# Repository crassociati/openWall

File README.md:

openWall
========

vertical plotting system

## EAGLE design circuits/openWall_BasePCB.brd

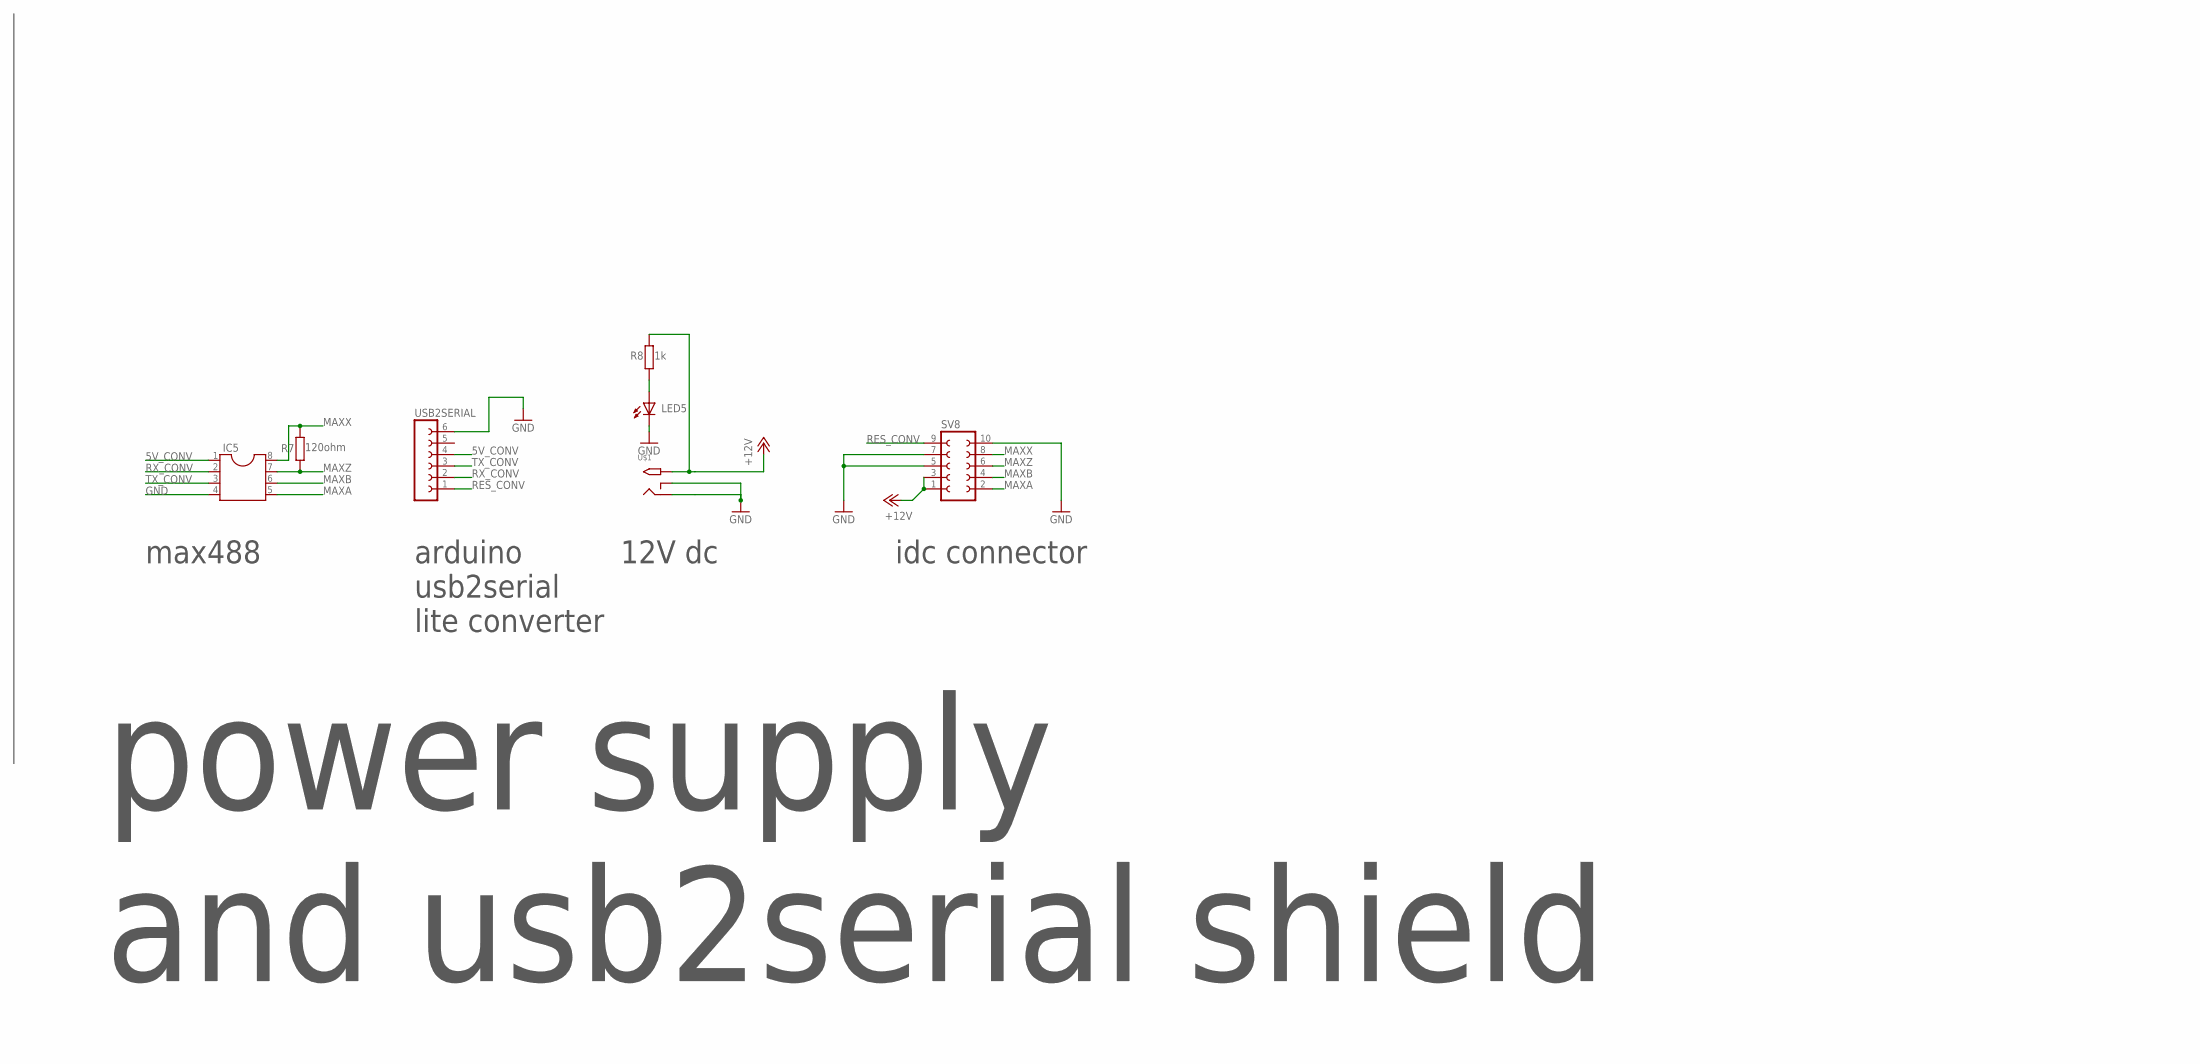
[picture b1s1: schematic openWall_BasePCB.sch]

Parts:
IC5: DIL8; DIL08
LED5: TLLG4400; LED3MM
R7: 120ohm; 0207/7
R8: 1k; 0207/7
SV8: FE05-2
U$1: 2.1MMJACKTHM; PJ-102A
USB2SERIAL: FE06-1; FE06

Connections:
5V_CONV: IC5.1, USB2SERIAL.4
12V: R8.2, U$1.TIP
+12V: SV8.1, SV8.3
GND: IC5.4, LED5.K (C), SV8.5, SV8.7, SV8.10, U$1.RING, U$1.RING_SW, USB2SERIAL.6
MAXA: IC5.5, SV8.2
MAXB: IC5.6, SV8.4
MAXX: IC5.8, R7.2, SV8.8
MAXZ: IC5.7, R7.1, SV8.6
unnamed: LED5.A, R8.1
RES_CONV: SV8.9, USB2SERIAL.1
RX_CONV: IC5.2, USB2SERIAL.2
TX_CONV: IC5.3, USB2SERIAL.3

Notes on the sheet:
arduino usb2serial lite converter
max488
12V dc
idc connector
power supply and usb2serial shield

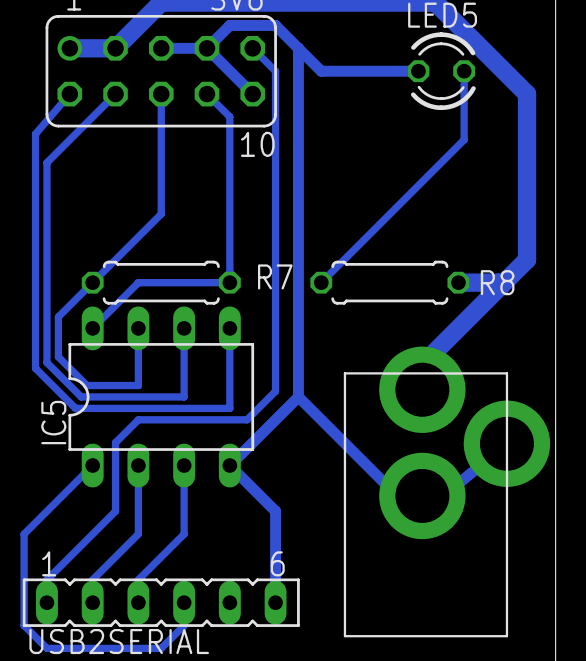
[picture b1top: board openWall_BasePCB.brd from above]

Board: 2 copper layers, 7 parts (0 on the bottom side), 12 nets.

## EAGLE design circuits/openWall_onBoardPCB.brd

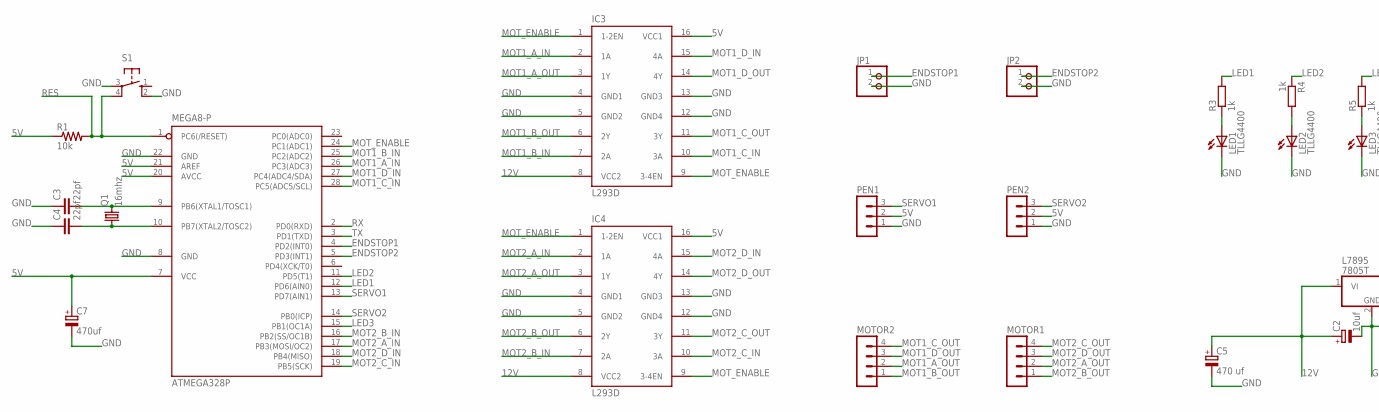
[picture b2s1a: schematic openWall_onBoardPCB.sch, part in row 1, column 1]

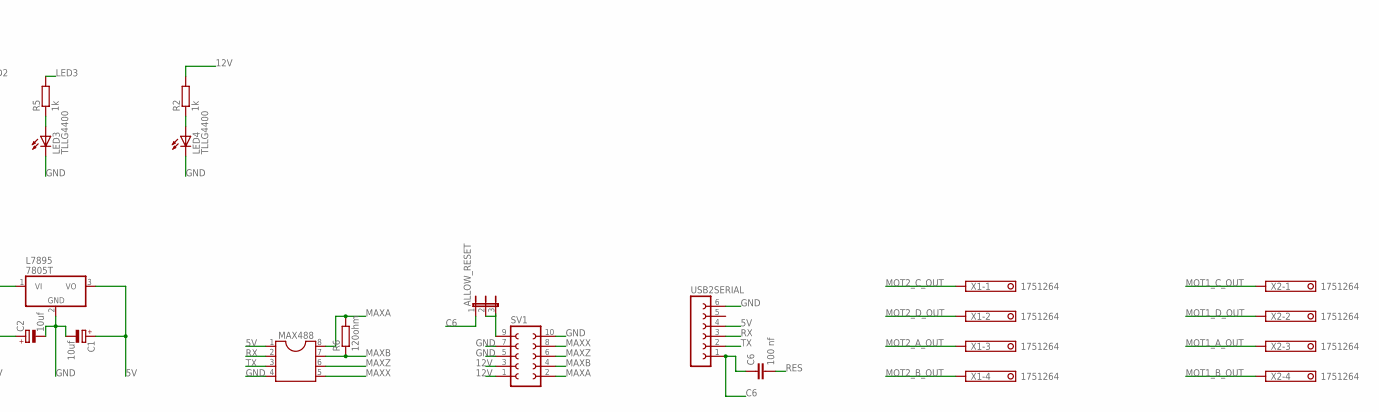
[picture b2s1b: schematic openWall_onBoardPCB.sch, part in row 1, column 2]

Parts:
ALLOW_RESET: JP2E; JP2
ATMEGA328P: MEGA8-P; DIL28-3
C1, C2: 10uf; E2,5-6
C3, C4: 22pf; C025-030X050
C5: 470 uf; E5-6
C6: 100 nf; C050-024X044
C7: 470uf; E5-6
IC3, IC4: L293D; DIL16
JP1, JP2: PINHD-1X2; 1X02
L7895: 7805T; TO220H
LED1, LED2, LED3, LED4: TLLG4400; LED3MM
MAX488: DIL8; DIL08
MOTOR1, MOTOR2: MA04-1
PEN1, PEN2: MA03-1
Q1: 16mhz; HC49/S
R1: 10k; 0207/7
R2: 1k; 0207/7
R3, R4, R5: 1k; 0309V
R6: 120ohm; 0207/7
S1: 10-XX; B3F-10XX
SV1: FE05-2
USB2SERIAL: FE06-1; FE06
X1, X2: 1751264

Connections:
5V: ATMEGA328P.7 (VCC), ATMEGA328P.20 (AVCC), ATMEGA328P.21 (AREF), C1.+, C7.+, IC3.16 (VCC1), IC4.16 (VCC1), L7895.3 (VO), MAX488.1, PEN1.2, PEN2.2, R1.1, USB2SERIAL.4
12V: C2.+, C5.+, IC3.8 (VCC2), IC4.8 (VCC2), L7895.1 (VI), R2.2, SV1.1, SV1.3
C6: ALLOW_RESET.1, C6.1, USB2SERIAL.1
ENDSTOP1: ATMEGA328P.4 (PD2(INT0)), JP1.1
ENDSTOP2: ATMEGA328P.5 (PD3(INT1)), JP2.1
GND: ATMEGA328P.8 (GND), ATMEGA328P.22 (GND), C1.-, C2.-, C3.1, C4.1, C5.-, C7.-, IC3.4 (GND1), IC3.5 (GND2), IC3.12 (GND4), IC3.13 (GND3), IC4.4 (GND1), IC4.5 (GND2), IC4.12 (GND4), IC4.13 (GND3), JP1.2, JP2.2, L7895.2 (GND), LED1.K (C), LED2.K (C), LED3.K (C), LED4.K (C), MAX488.4, PEN1.1, PEN2.1, S1.2 (S1), S1.3, SV1.5, SV1.7, SV1.10, USB2SERIAL.6
LED1: ATMEGA328P.12 (PD6(AIN0)), R3.2
LED2: ATMEGA328P.11 (PD5(T1)), R4.1
LED3: ATMEGA328P.15 (PB1(OC1A)), R5.2
MAXA: MAX488.8, R6.2, SV1.2
MAXB: MAX488.7, R6.1, SV1.4
MAXX: MAX488.5, SV1.8
MAXZ: MAX488.6, SV1.6
MOT1_A_IN: ATMEGA328P.26 (PC3(ADC3)), IC3.2 (1A)
MOT1_A_OUT: IC3.3 (1Y), MOTOR2.2, X2.3
MOT1_B_IN: ATMEGA328P.25 (PC2(ADC2)), IC3.7 (2A)
MOT1_B_OUT: IC3.6 (2Y), MOTOR2.1, X2.4
MOT1_C_IN: ATMEGA328P.28 (PC5(ADC5/SCL)), IC3.10 (3A)
MOT1_C_OUT: IC3.11 (3Y), MOTOR2.4, X2.1
MOT1_D_IN: ATMEGA328P.27 (PC4(ADC4/SDA)), IC3.15 (4A)
MOT1_D_OUT: IC3.14 (4Y), MOTOR2.3, X2.2
MOT2_A_IN: ATMEGA328P.17 (PB3(MOSI/OC2)), IC4.2 (1A)
MOT2_A_OUT: IC4.3 (1Y), MOTOR1.2, X1.3
MOT2_B_IN: ATMEGA328P.16 (PB2(SS/OC1B)), IC4.7 (2A)
MOT2_B_OUT: IC4.6 (2Y), MOTOR1.1, X1.4
MOT2_C_IN: ATMEGA328P.19 (PB5(SCK)), IC4.10 (3A)
MOT2_C_OUT: IC4.11 (3Y), MOTOR1.4, X1.1
MOT2_D_IN: ATMEGA328P.18 (PB4(MISO)), IC4.15 (4A)
MOT2_D_OUT: IC4.14 (4Y), MOTOR1.3, X1.2
MOT_ENABLE: ATMEGA328P.24 (PC1(ADC1)), IC3.1 (1-2EN), IC3.9 (3-4EN), IC4.1 (1-2EN), IC4.9 (3-4EN)
unnamed: ATMEGA328P.10 (PB7(XTAL2/TOSC2)), C4.2, Q1.1
unnamed: ATMEGA328P.9 (PB6(XTAL1/TOSC1)), C3.2, Q1.2
unnamed: LED1.A, R3.1
unnamed: LED4.A, R2.1
unnamed: LED2.A, R4.2
unnamed: LED3.A, R5.1
unnamed: ALLOW_RESET.2, ALLOW_RESET.3
RES: ATMEGA328P.1 (PC6(/RESET)), C6.2, R1.2, S1.4 (P1)
RX: ATMEGA328P.2 (PD0(RXD)), MAX488.2, USB2SERIAL.3
SERVO1: ATMEGA328P.13 (PD7(AIN1)), PEN1.3
SERVO2: ATMEGA328P.14 (PB0(ICP)), PEN2.3
TX: ATMEGA328P.3 (PD1(TXD)), MAX488.3, USB2SERIAL.2

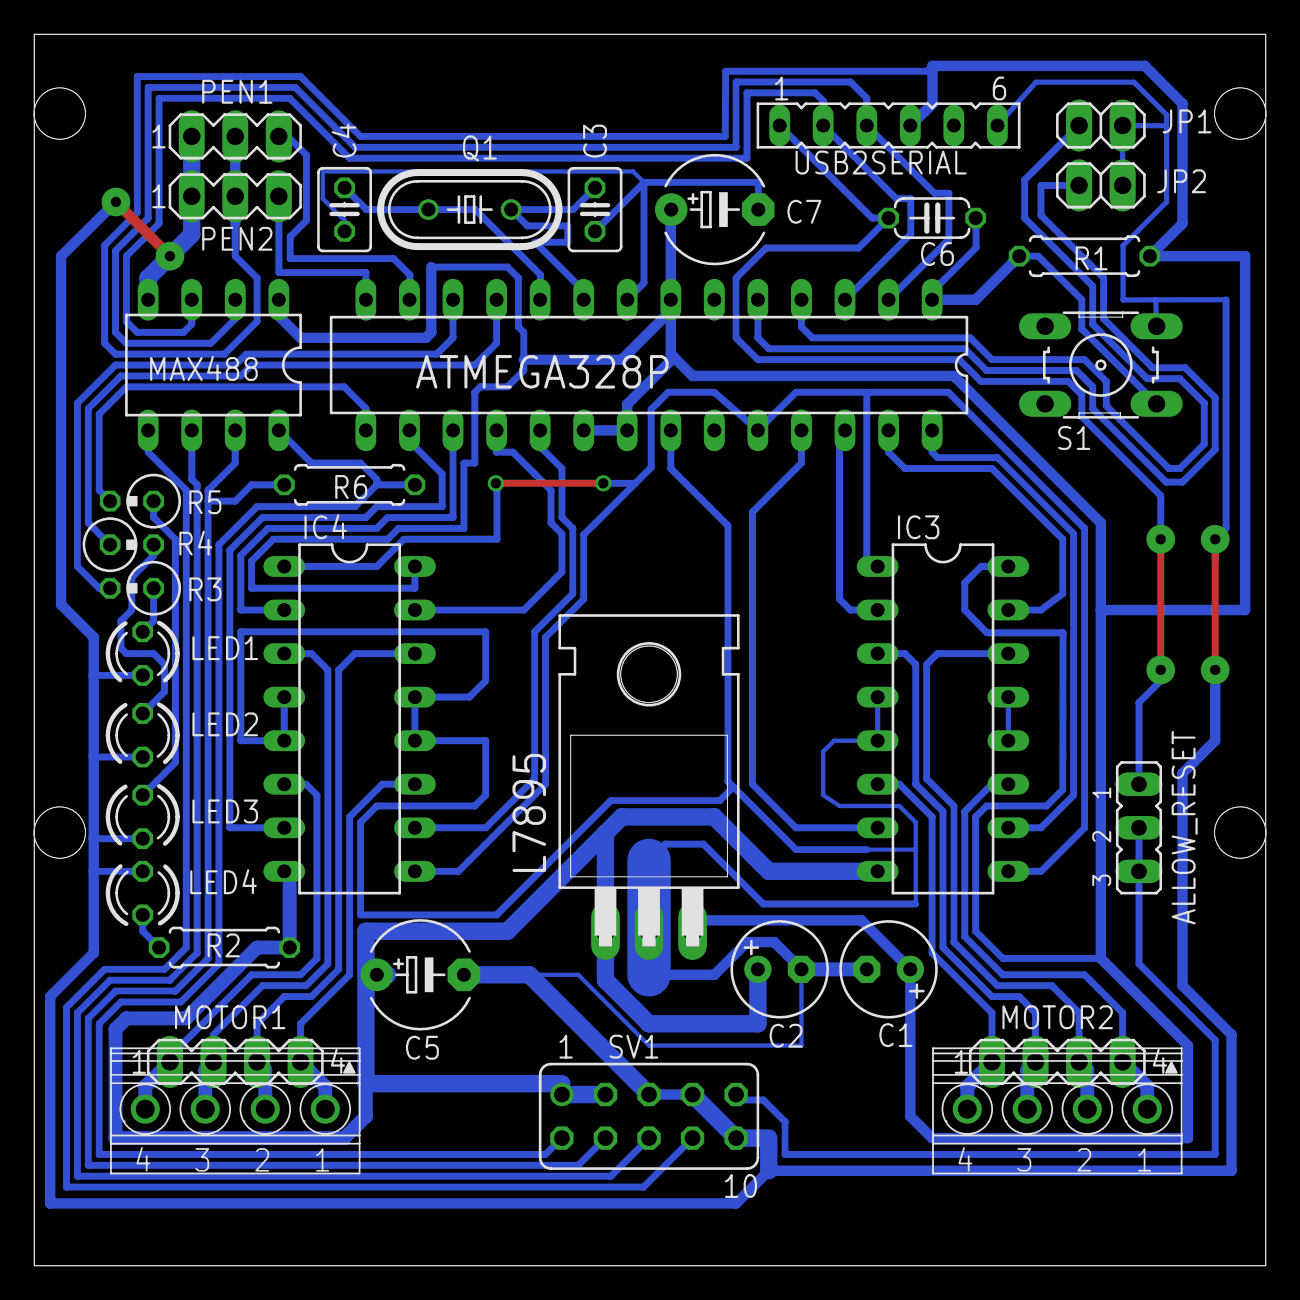
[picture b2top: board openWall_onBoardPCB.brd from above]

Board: 2 copper layers, 71.8 x 71.8 mm, 35 parts (0 on the bottom side), 42 nets.

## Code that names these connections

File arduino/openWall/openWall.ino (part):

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#include <Servo.h>

// Pins
#define LED1_PIN 9
#define LED2_PIN 5
#define LED3_PIN 6
#define PEN_SERVO_PIN 7
#define STEPPER_ENABLE_PIN A1

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{
  Serial.begin(9600);

  pinMode(LED1_PIN, OUTPUT);
  pinMode(LED2_PIN, OUTPUT);
  pinMode(LED3_PIN, OUTPUT);
  digitalWrite(LED1_PIN, LOW);
  digitalWrite(LED2_PIN, LOW);
  digitalWrite(LED3_PIN, LOW);

  pinMode(STEPPER_ENABLE_PIN, OUTPUT);
  digitalWrite(STEPPER_ENABLE_PIN, HIGH); 
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  {
    // Move, no write, fast speed
    
    digitalWrite(LED1_PIN, LOW);
    digitalWrite(LED2_PIN, HIGH);

    setSteppersSpeed(fastStepperSpeed);

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  {
    // Write while moving, slow speed
    
    digitalWrite(LED1_PIN, HIGH);
    digitalWrite(LED2_PIN, LOW);

    setSteppersSpeed(slowStepperSpeed);

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  {
    // Move the steppers and write. fast speed

    digitalWrite(LED1_PIN, LOW);

    setSteppersSpeed(fastStepperSpeed);

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  {
    // Move the steppers, no write, fast speed

    digitalWrite(LED1_PIN, LOW); 

    setSteppersSpeed(fastStepperSpeed);

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  {
    // Move the steppers and write. fast speed

    digitalWrite(LED1_PIN, LOW); 
 
    setSteppersSpeed(fastStepperSpeed);
 
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  {
    // Initial calibration, no move
    
    digitalWrite(LED3_PIN, HIGH);

    leftStepperPosition = commandParam1;
    rightStepperPosition = commandParam2;
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

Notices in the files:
arduino/openWall/openWall.ino:
Copyright (C) 2013  Pietro Leoni
This program is free software: you can redistribute it and/or modify
it under the terms of the GNU General Public License as published by
the Free Software Foundation, either version 3 of the License, or
(at your option) any later version.
